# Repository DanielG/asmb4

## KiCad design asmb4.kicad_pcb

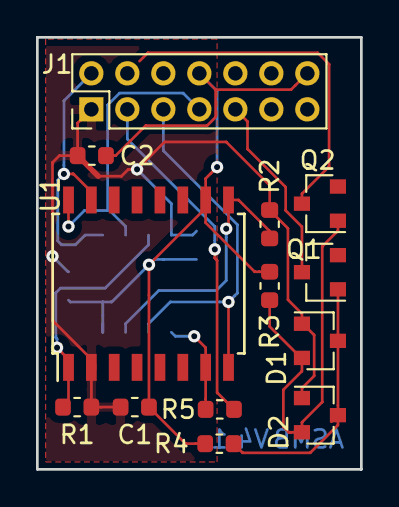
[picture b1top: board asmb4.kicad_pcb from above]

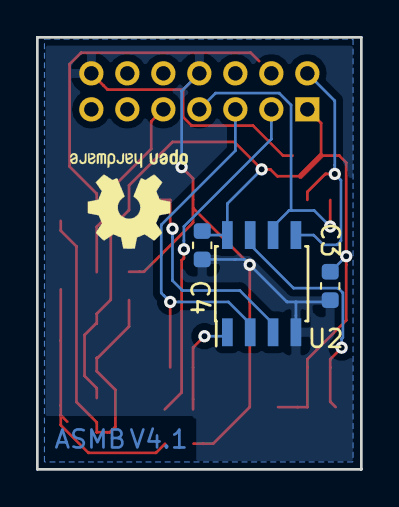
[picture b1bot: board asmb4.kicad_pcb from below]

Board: 2 copper layers, 18.0 x 24.0 mm, 16 parts (3 on the bottom side), 13 nets.

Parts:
C1, C2, C3, C4: C; C_0603_1608Metric
D1, D2: D_x2_ACom_AKK; SOT-23
J1: Conn_02x07_Odd_Even; PinHeader_2x07_P2.00mm_Vertical
Q1, Q2: D; D_SOT-23_ANK
R1, R2, R3, R4, R5: R; R_0603_1608Metric
U1: SPI25-16; SOIC-16W_7.5x10.3mm_P1.27mm
U2: SPI25-8; SOIC-8_3.9x4.9mm_P1.27mm

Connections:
/Q1.1: J1.9, Q1.1
/Q2.1: J1.4, Q2.1
/SCK: J1.7, U1.16, U2.6
/SI: J1.2, U1.15, U2.5
/SO: J1.5, U1.8, U2.2
/~CS: R5.1, U1.7, U2.1
/~HOLD: R1.2, U1.1, U2.7
/~WP: R2.2, U1.9, U2.3
GND: C1.2, C2.2, C3.2, C4.2, J1.8, J1.14, R3.1, R4.1, U1.10, U2.4
unnamed: D1.2, D2.2, Q2.2, R3.2
unnamed: D1.3, D2.3, Q1.2, R4.2
unnamed: J1.3, R5.2
VCC: C1.1, C2.1, C3.1, C4.1, D1.1, D2.1, J1.1, R1.1, R2.1, U1.2, U2.8

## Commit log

2018-11-03 Initial version
